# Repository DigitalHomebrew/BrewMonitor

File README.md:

BrewMonitor
===========
Brewing beer is great fun and super rewarding. You're in control of the process and whether you're brewing a kit & kilo, or a complex all grain recipe, in just a few hours you can produce top quality wort for your next award winning home brew. After brew day, the next step is fermentation and this is where the whole process can easily come unstuck. During fermentation your yeast is in control and it can take days, weeks or even months to do its job. Yeast is a living organism and doesn't always behave the way we expect which is why it pays to keep regular tabs on your fermentation and avoid any nasty surprises. Keeping a close watch on fermentation is repetitive and time consuming - a perfect candidate for automation with a system like BrewMonitor.

BrewMonitor monitors and records your home brew's fermentation activity while you're not around. It's like having a super-dedicated assistant brewer working 24/7. This frees you up to go about your daily life in confidence that your fermentation is still being monitored diligently and you can check up on it remotely at any time.

The concept is pretty simple - to hook up a recording device to your fermenter that monitors temperature and airlock activity. That way you can easily answer important questions that would otherwise have required constant observation, such as:
* "What was my lag time?" - An indicator of yeast viability, health and pitching rate.
* "Is fermentation slowing down yet?" - Good to know if you want to perform a diacetyl rest.
* "How long ago did it stop bubbling?" - Might be time to take some final gravity readings to prepare for bottling.
* "What was my peak temperature during fermentation?" - Necessary to accurately calculate priming additions.

##The hardware
The BrewMonitor is an AVR based circuit that interfaces a digital temperature probe as well as an infrared light gate to monitor bubbles passing through your air lock. It has onboard memory for recording fermentation data and supports PC connectivity over USB.

Fermentation activity is monitored by counting the bubbles as they pass through a gooseneck airlock. Rather than telling you "how much" your beer has fermented, watching the airlock gives you an indication of "how active" your fermentation currently is. The bubbles are detected using an infrared light gate and the signal is interpreted with an ADC in the microcontroller.

BrewMonitor's hardware is completely open source. The eagle files for the PCB are included in this repository along with the 3D .stl files for printing an airlock sensor.

##The software
The BrewMonitor application is written in C#.NET and runs on windows. It has three main purposes:
1. Downloading, Exploring and Exporting data from your BrewMonitor
2. Configuring your BrewMonitor's sensors
3. Managing notifications that can be pushed to your phone during fermentation

From the "explore" tab, you can download the data from your BrewMonitor's internal memory for review and export. Clicking on the export button allows you to save the data in .csv format so you can open it in Excel or other software.

Using the "configure" tab, you're able to tune the parameters of your airlock sensor. In this window you can see raw data streaming from the brewmonitor's sensor and drag the slider bars to determine the mean values and hysteresis to accurately detect the passage of each bubble.

##The cloud
The major goal of the BrewMonitor is to free you up to go about your daily life without having to keep regular tabs on your fermentation. By integrating with thingspeak.com BrewMonitor's data can be accessed from a computer or mobile device wherever you are - great for brewers that like to watch their yeast reproduce over the internet ;) Also, by integrating with pushover.net the BrewMonitor can send push notifications directly to your phone when milestomes are reached or intervention is required.

These notifications are configured using the "monitor" tab of the brewmonitor software which is still under heavy development at this point in time.

We're currently working on a number of notifications like:
"You've reached 17C, it's time to pitch your yeast!"
"Your temperature has crept up to 25C. You might wanna ice-bath that baby"
"Your bubble rate has slowed to 50% of its peak, now might be a good time for a diacetyl rest"
"Your airlock has been nactive for a while. Time to take some S.G. readings and free up a keg"

#Project status
While a lot of work has gone into the BrewMonitor project as it stands, there is still plenty of work to be carried out.

1. Finish plumbing and testing pushover and thingspeak integration
2. Allow the BrewMonitor to talk directly with the cloud over WiFi
3. Update the hardware to make it easier for others to build and contribute

You can follow the BrewMonitor discussion over at [the AussieHomebrewer forum here](http://aussiehomebrewer.com/topic/88881-brewmonitor-project/).

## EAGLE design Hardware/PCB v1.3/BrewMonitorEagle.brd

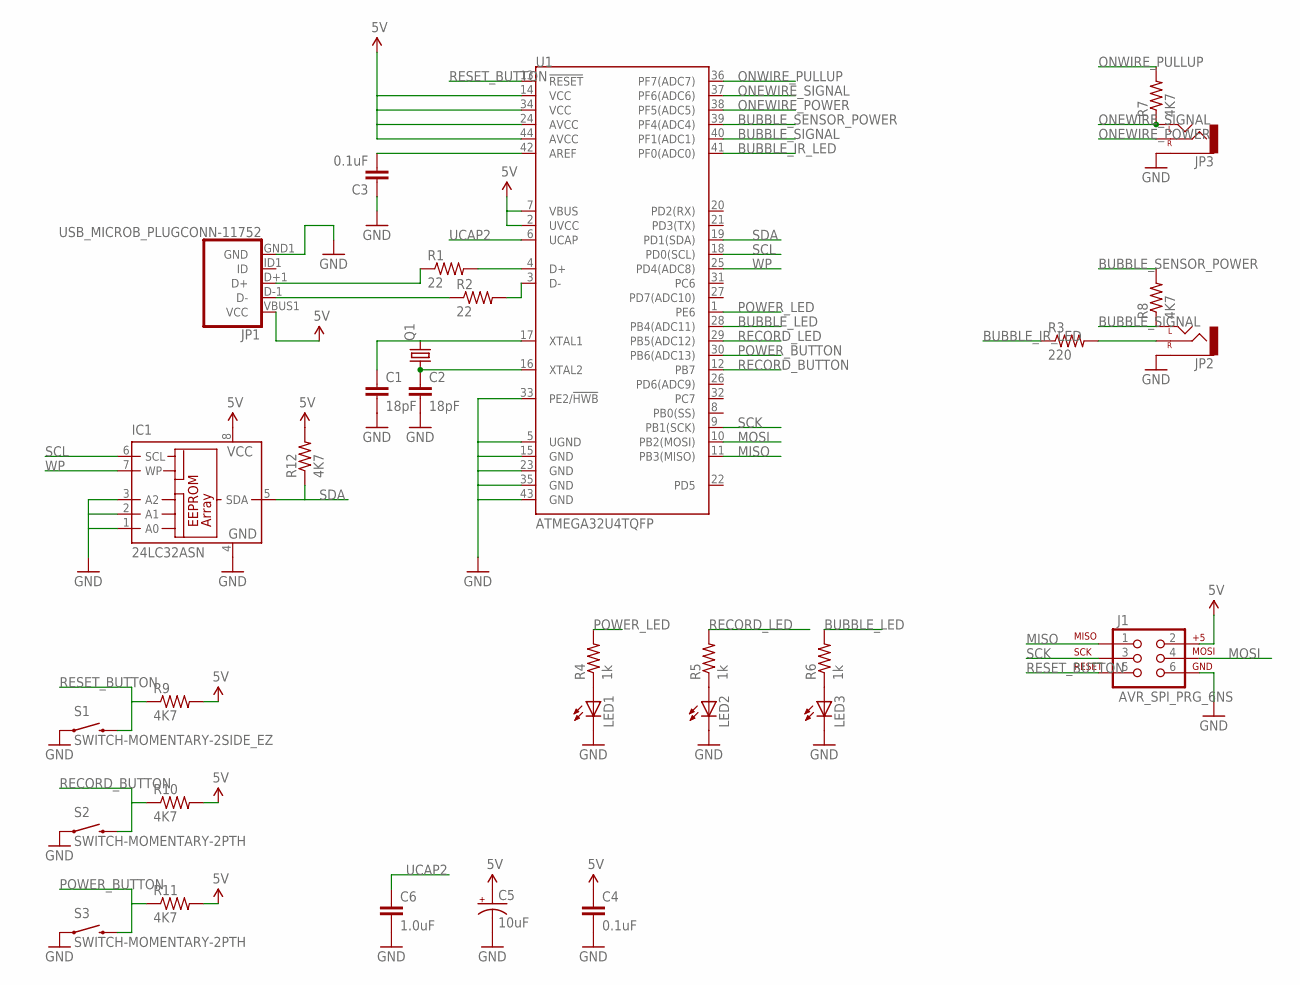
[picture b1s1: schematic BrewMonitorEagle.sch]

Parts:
C1, C2: 18pF; 0603-CAP
C3, C4: 0.1uF; 0603-CAP
C5: 10uF; EIA3216
C6: 1.0uF; 0603-CAP
IC1: 24LC32ASN; SO-08
J1: AVR_SPI_PRG_6NS; 2X3-NS
JP1: USB_MICROB_PLUGCONN-11752; USB-B-MICRO-SMD_V03
JP2, JP3: AUDIO-JACKSMD2; AUDIO-JACK-3.5MM-SMD
LED1, LED2, LED3: LED-3MM-NO_SILK; LED3MM-NS
Q1: CRYSTALHC49UP; HC49UP
R1, R2: 22; 0603-RES
R3: 220; 0603-RES
R4, R5, R6: 1k; 0603-RES
R7, R8, R9, R10, R11, R12: 4K7; 0603
S1: SWITCH-MOMENTARY-2SIDE_EZ; TACTILE-PTH-SIDEEZ
S2, S3: SWITCH-MOMENTARY-2PTH; TACTILE-PTH
U1: ATMEGA32U4TQFP; SPARKFUN-DIGITALIC_TQFP44

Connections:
5V: C4.1, C5.A (+), IC1.8 (VCC), J1.2, JP1.VBUS1 (VCC), R9.2, R10.2, R11.2, R12.2, U1.2 (UVCC), U1.7 (VBUS), U1.14 (VCC), U1.24 (AVCC), U1.34 (VCC), U1.44 (AVCC)
BUBBLE_IR_LED: R3.1, U1.41 (PF0(ADC0))
BUBBLE_LED: R6.2, U1.28 (PB4(ADC11))
BUBBLE_SENSOR_POWER: R8.2, U1.39 (PF4(ADC4))
BUBBLE_SIGNAL: JP2.TIP (LEFT), R8.1, U1.40 (PF1(ADC1))
GND: C1.2, C2.2, C3.1, C4.2, C5.C (-), C6.2, IC1.1 (A0), IC1.2 (A1), IC1.3 (A2), IC1.4 (GND), J1.6, JP1.GND1 (GND), JP2.SLEEVE, JP3.SLEEVE, LED1.K (C), LED2.K (C), LED3.K (C), S1.1, S2.1, S3.1, U1.5 (UGND), U1.15 (GND), U1.23 (GND), U1.33 (PE2/!HWB), U1.35 (GND), U1.43 (GND)
MISO: J1.1, U1.11 (PB3(MISO))
MOSI: J1.4, U1.10 (PB2(MOSI))
unnamed: R2.2, U1.3 (D-)
unnamed: R1.2, U1.4 (D+)
unnamed: C1.1, Q1.2, U1.17 (XTAL1)
unnamed: C2.1, Q1.1, U1.16 (XTAL2)
unnamed: JP1.D-1 (D-), R2.1
unnamed: JP1.D+1 (D+), R1.1
unnamed: C3.2, U1.42 (AREF)
unnamed: LED1.A, R4.1
unnamed: LED2.A, R5.1
unnamed: LED3.A, R6.1
unnamed: JP2.RING (RIGHT), R3.2
ONEWIRE_POWER: JP3.RING (RIGHT), U1.38 (PF5(ADC5))
ONEWIRE_SIGNAL: JP3.TIP (LEFT), R7.1, U1.37 (PF6(ADC6))
ONWIRE_PULLUP: R7.2, U1.36 (PF7(ADC7))
POWER_BUTTON: R11.1, S3.3 (2), U1.30 (PB6(ADC13))
POWER_LED: R4.2, U1.1 (PE6)
RECORD_BUTTON: R10.1, S2.3 (2), U1.12 (PB7)
RECORD_LED: R5.2, U1.29 (PB5(ADC12))
RESET_BUTTON: J1.5, R9.1, S1.2, U1.13 (!RESET)
SCK: J1.3, U1.9 (PB1(SCK))
SCL: IC1.6 (SCL), U1.18 (PD0(SCL))
SDA: IC1.5 (SDA), R12.1, U1.19 (PD1(SDA))
UCAP2: C6.1, U1.6 (UCAP)
WP: IC1.7 (WP), U1.25 (PD4(ADC8))

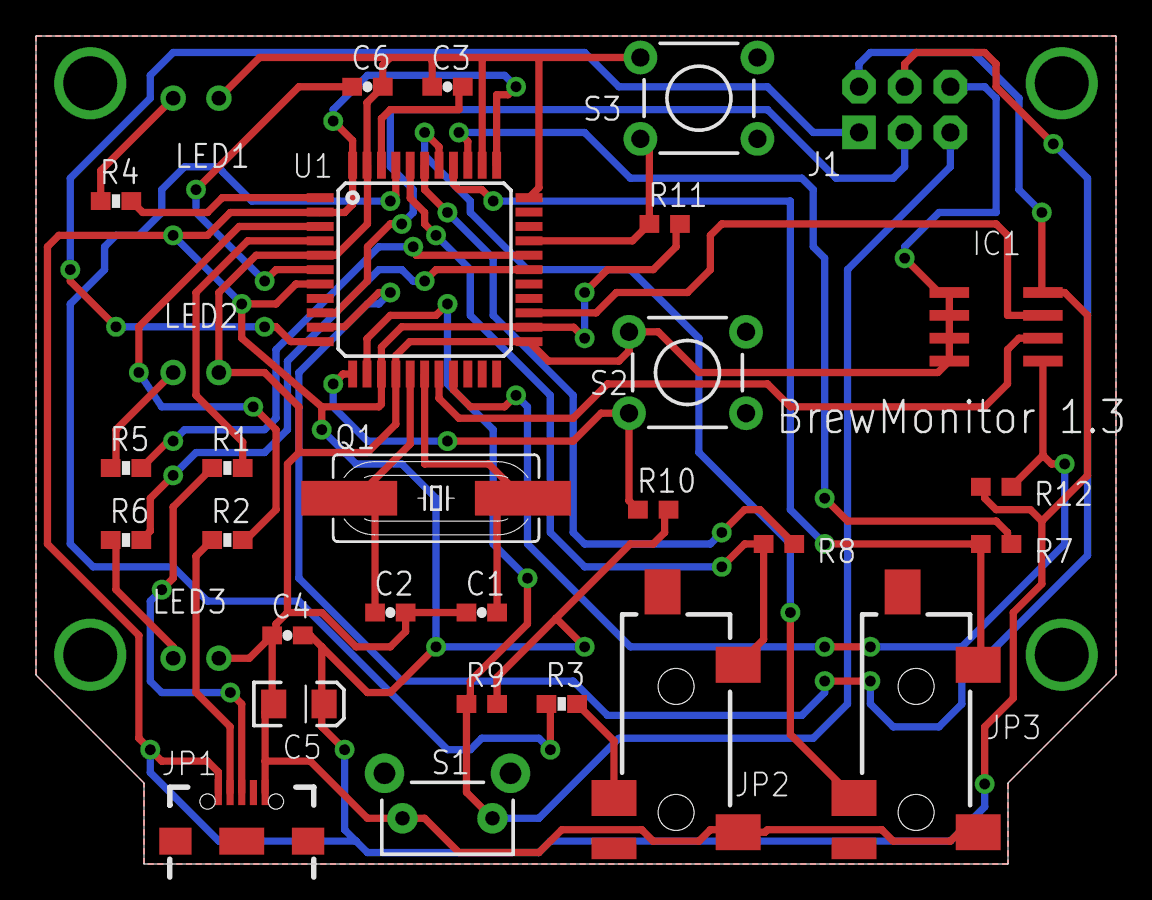
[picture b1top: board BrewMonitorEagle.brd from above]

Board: 2 copper layers, 60.0 x 46.0 mm, 31 parts (0 on the bottom side), 32 nets.

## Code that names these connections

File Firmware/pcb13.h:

/*
 * pcb13.h
 * IO Mappings for BrewMonitor PCB version 1.3
 * Created: 29/05/2014 9:40:58 AM
 *  Author: Michael
 */ 

#ifndef PCB13_H_
#define PCB13_H_

// Define IO
#define RECORD_LED_PORT PORTB
#define RECORD_LED_PIN PIN5
#define RECORD_LED_DDR DDRB

#define RECORD_BUTTON_INPORT PINB
#define RECORD_BUTTON_PIN PIN7
#define RECORD_BUTTON_DDR DDRB

#define BUBBLE_SENSOR_INPORT PINF
#define BUBBLE_SENSOR_DDR DDRF
#define BUBBLE_SENSOR_PIN PIN1

#define BUBBLE_SENSOR_PULLUP_PORT PORTF
#define BUBBLE_SENSOR_PULLUP_PIN PIN4
#define BUBBLE_SENSOR_PULLUP_DDR DDRF

#define BUBBLE_IR_LED_PORT PORTF
#define BUBBLE_IR_LED_PIN PIN0
#define BUBBLE_IR_LED_DDR DDRF

#define BUBBLE_LED_PORT PORTB
#define BUBBLE_LED_PIN PIN4
#define BUBBLE_LED_DDR DDRB

#define ONEWIRE_DATA_PORT PORTF
#define ONEWIRE_DATA_INPORT PINF
#define ONEWIRE_DATA_PIN PIN6
#define ONEWIRE_DATA_DDR DDRF

#define ONEWIRE_POWER_DDR DDRF
#define ONEWIRE_POWER_PORT PORTF
#define ONEWIRE_POWER_INPORT PINF
#define ONEWIRE_POWER_PIN PIN5

#define ONEWIRE_PULLUP_PORT PORTF
#define ONEWIRE_PULLUP_INPORT PINF
#define ONEWIRE_PULLUP_PIN PIN7
#define ONEWIRE_PULLUP_DDR DDRF

#define EEPROM_WP_DDR DDRD
#define EEPROM_WP_PIN PIN4
#define EEPROM_SCL_DDR DDRD
#define EEPROM_SCL_PORT PORTD
#define EEPROM_SCL_PIN PIN0
#define EEPROM_SDA_DDR DDRD
#define EEPROM_SDA_PIN PIN1

#endif /* PCB13_H_ */

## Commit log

2015-11-24 Updated readme.md a little
    Still needs much work.
2015-11-24 Initial code commit
2015-11-24 Remaining changes
2015-11-24 Removed unnecessary files.
2015-11-24 Moved design filed into /resources
2015-11-24 Added firmware to repo
    Added the Atmel studio solution for the brewmonitor firmware
2015-11-24 Added eagle files for v1.3 PCB
2015-11-24 Added more text describing this project
2015-11-24 Added pics for intro page
    These are referenced in the readme.md for the project homepage.
    The pics are of the brewmonitor, pcb, sensor and screenshots.
2015-11-24 Added pics to Readme.md
2015-11-24 More updated to readme.md
2015-11-24 Added IOS notification screenshot
2015-11-24 renamed notification screenshot
2015-11-24 Added ios thingspeak screenshot
2015-11-26 Added thingspeak integration and saving settings. Also working on pushover integration but not complete yet.
2015-11-26 Pushover notifications are now working!
2015-11-27 Added BrewMonitor sketch
2015-11-27 Started working on Control tab for temperature control
2015-11-30 Renamed PCB folder
2015-12-02 Removed Control tab from main view model
2015-12-02 Added Airlock Sensor stl file
2015-12-02 Added Power Control

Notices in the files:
parts and their libraries:
SparkFun-DigitalIC: Licensing: CC v3.0 Share-Alike You are welcome to use this library for commercial purposes.
